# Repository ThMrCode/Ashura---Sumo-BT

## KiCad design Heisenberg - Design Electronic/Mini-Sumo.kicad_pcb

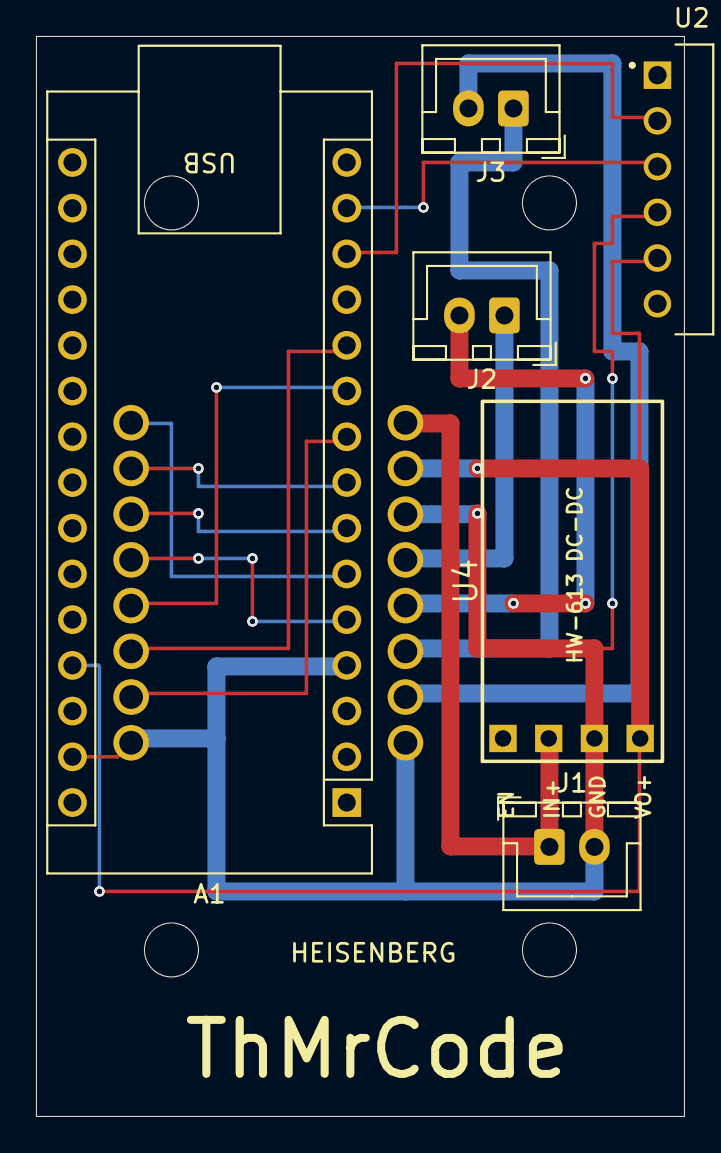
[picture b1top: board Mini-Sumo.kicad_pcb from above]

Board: 2 copper layers, 36.0 x 60.0 mm, 7 parts (1 on the bottom side), 16 nets.

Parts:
A1: Arduino_Nano_v3.x; Arduino_Nano
J1, J2, J3: Conn_01x02_Pin; JST_XH_B2B-XH-A_1x02_P2.50mm_Vertical
U1: ROB-14450; MODULE_ROB-14450
U2: ZC142200; MODULE_ZC142200
U4: HW-613 DC-DC; HW-613 DC-DC MODULE

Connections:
+5V: A1.27 (+5V), U1.2 (VCC), U2.5 (VCC), U4.4 (VO+)
+12V: J1.1, U1.1 (VM), U4.2 (IN+)
DIGITAL_CONTROL_AI1: A1.7 (D4), U1.14 (AI1)
DIGITAL_CONTROL_AI2: A1.8 (D5), U1.15 (AI2)
DIGITAL_CONTROL_BI1: A1.10 (D7), U1.12 (BI1)
DIGITAL_CONTROL_BI2: A1.11 (D8), U1.11 (BI2)
GND: A1.4 (GND), A1.29 (GND), J1.2, U1.3 (GND), U1.8 (GND), U1.9 (GND), U2.4 (GND), U4.3 (GND)
HC05_TO_NANO: A1.13 (D10), U2.2 (RX)
MOTOR_A01: J2.1, U1.4 (A01)
MOTOR_A02: J2.2, U1.5 (A02)
MOTOR_B01: J3.2, U1.7 (B01)
MOTOR_B02: J3.1, U1.6 (B02)
NANO_TO_HC05: A1.14 (D11), U2.3 (TX)
PWM_A: A1.6 (D3), U1.16 (PWMA)
PWM_B: A1.9 (D6), U1.10 (PWMB)
STBY: A1.5 (D2), U1.13 (STBY)

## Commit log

2025-01-28 Heisenberg Version 1.0
2025-03-06 Subida Pseudo Final
2025-03-06 Subida Inicial
2025-04-23 Subida Final
2025-04-24 Heisenberg BT Firmware V2 Module Acelerator
2025-04-24 The Ashura Firmware Beta
